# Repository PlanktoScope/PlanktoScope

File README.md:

# PlanktoScope: Open and Affordable Quantitative Imaging Platform

## What are Plankton?

_"Drifting endlessly, midway between the sea of air above and the depths of the abyss below, these strange creatures and the marine inflorescence that sustains them are called 'plankton' — the wanderers"_ - **[Rachel Carson](https://en.wikipedia.org/wiki/Rachel_Carson)**

Plankton are tiny organisms that drift in the oceans and play a crucial role in the global ecosystem. They are responsible for fixing 30-50% of the world's carbon dioxide and form the foundation of the global food chain. Despite their importance, studying plankton can be challenging due to the vast area of the oceans and the limited resources of research fleets and specialized equipment. The PlanktoScope is an open-source hardware and software platform that aims to make it easier to study plankton by providing high-throughput quantitative imaging capabilities at a low cost.

## What is a PlanktoScope?

The PlanktoScope is a modular, open-source platform for high-throughput quantitative imaging of plankton samples. Its small size, ease of use, and low cost make it suitable for a variety of applications, including the monitoring of laboratory cultures or natural micro-plankton communities. It can be controlled from any WiFi-enabled device and can be easily reconfigured to meet the changing needs of the user.

[Learn more about how it works](https://www.planktoscope.org/how-it-works)

## Read the Paper

The PlanktoScope has been described in the article ["PlanktoScope: Affordable Modular Quantitative Imaging Platform for Citizen Oceanography"](https://www.frontiersin.org/articles/10.3389/fmars.2022.949428/full), published in Frontiers in Marine Science in July 2022.

DOI: [https://doi.org/10.3389/fmars.2022.949428](https://doi.org/10.3389/fmars.2022.949428)

## Key Features

Here are some key features of the PlanktoScope:

1. **Low cost**: The PlanktoScope is designed to be affordable, with parts costing under $1000.
2. **Modular**: The PlanktoScope is modular, meaning it can be easily reconfigured to meet the changing needs of users.
3. **Open-source**: The PlanktoScope is based on open-source hardware and software, making it accessible to a wide community of engineers, researchers, and citizens.
4. **Versatility**: The PlanktoScope is versatile, and can be used to study a variety of plankton types, including laboratory cultures and natural micro-plankton communities.
5. **High-throughput**: The PlanktoScope is capable of high-throughput quantitative imaging, allowing users to analyze large numbers of samples quickly and efficiently.
6. **WiFi-enabled**: The PlanktoScope can be controlled from any WiFi-enabled device, making it easy to use and deploy in a variety of settings.
7. **Portable**: The PlanktoScope is small and portable, making it easy to transport and use in the field.
8. **Ease of use**: The PlanktoScope is designed to be easy to use, with instructions for assembly and use available on the PlanktoScope website.

## How do I get one?

You can access the complete documentation here: https://planktoscope.github.io/PlanktoScope/
|Get the kit|Assemble your kit|Start your machine|
|--|--|--|
||||

## Getting Involved

There are several ways you can join the development effort and contribute to this project.

### Communication Platform

We use Slack as a communication platform for interested parties. You can request to join by filling out [this form](https://docs.google.com/forms/d/e/1FAIpQLSfcod-avpzWVmWj42_hW1v2mMSHm0DAGXHxVECFig2dnKHxGQ/viewform).

### Reporting Issues

If you have identified a bug in the software or hardware, please open an issue in this repository to report it.

### Contributing to Development

You can also contribute to the development effort by working on open issues. Check out the [issues labeled as good first issues](https://github.com/PlanktoScope/PlanktoScope/labels/good%20first%20issue) and let us know in the comments if you are interested in working on one. We may be able to provide guidance as you get started with the code.

## License Information

This repository contains various types of materials that are covered by different licenses. Please read the following information carefully to determine which license applies to the materials you wish to use.

### Hardware Files

All hardware files and documentation located in the `hardware` directory are released under the [CERN-OHL-S-2.0](https://ohwr.org/cern_ohl_s_v2.txt) license.

### Software Source Code

The source code is released under the [GPL-3.0](https://www.gnu.org/licenses/gpl-3.0.en.html) license.

### Other Materials

All other materials, including documentation and pictures, are released under the [Creative Commons CC-BY-SA 4.0](https://creativecommons.org/licenses/by-sa/4.0/) license.

If you wish to use any of the materials in this repository for a project that cannot be open-sourced, please contact us using Slack so we can discuss potential solutions.

We encourage you to fork this repository and publish any improvements you make. Doing so helps others and allows us to potentially integrate your changes into this repository.

## Citing PlanktoScope

If you use PlanktoScope in your research, please use the following BibTeX entry.

```
@article{Pollina2022PlanktoScope,
  author={Pollina, Thibaut and Larson, Adam G. and Lombard, Fabien and Li, Hongquan and Le Guen, David and Colin, Sébastien and de Vargas, Colomban and Prakash, Manu},
  title={PlanktoScope: Affordable Modular Quantitative Imaging Platform for Citizen Oceanography},
  journal={Frontiers in Marine Science},
  year={2022},
  doi={10.3389/fmars.2022.949428}
}
```

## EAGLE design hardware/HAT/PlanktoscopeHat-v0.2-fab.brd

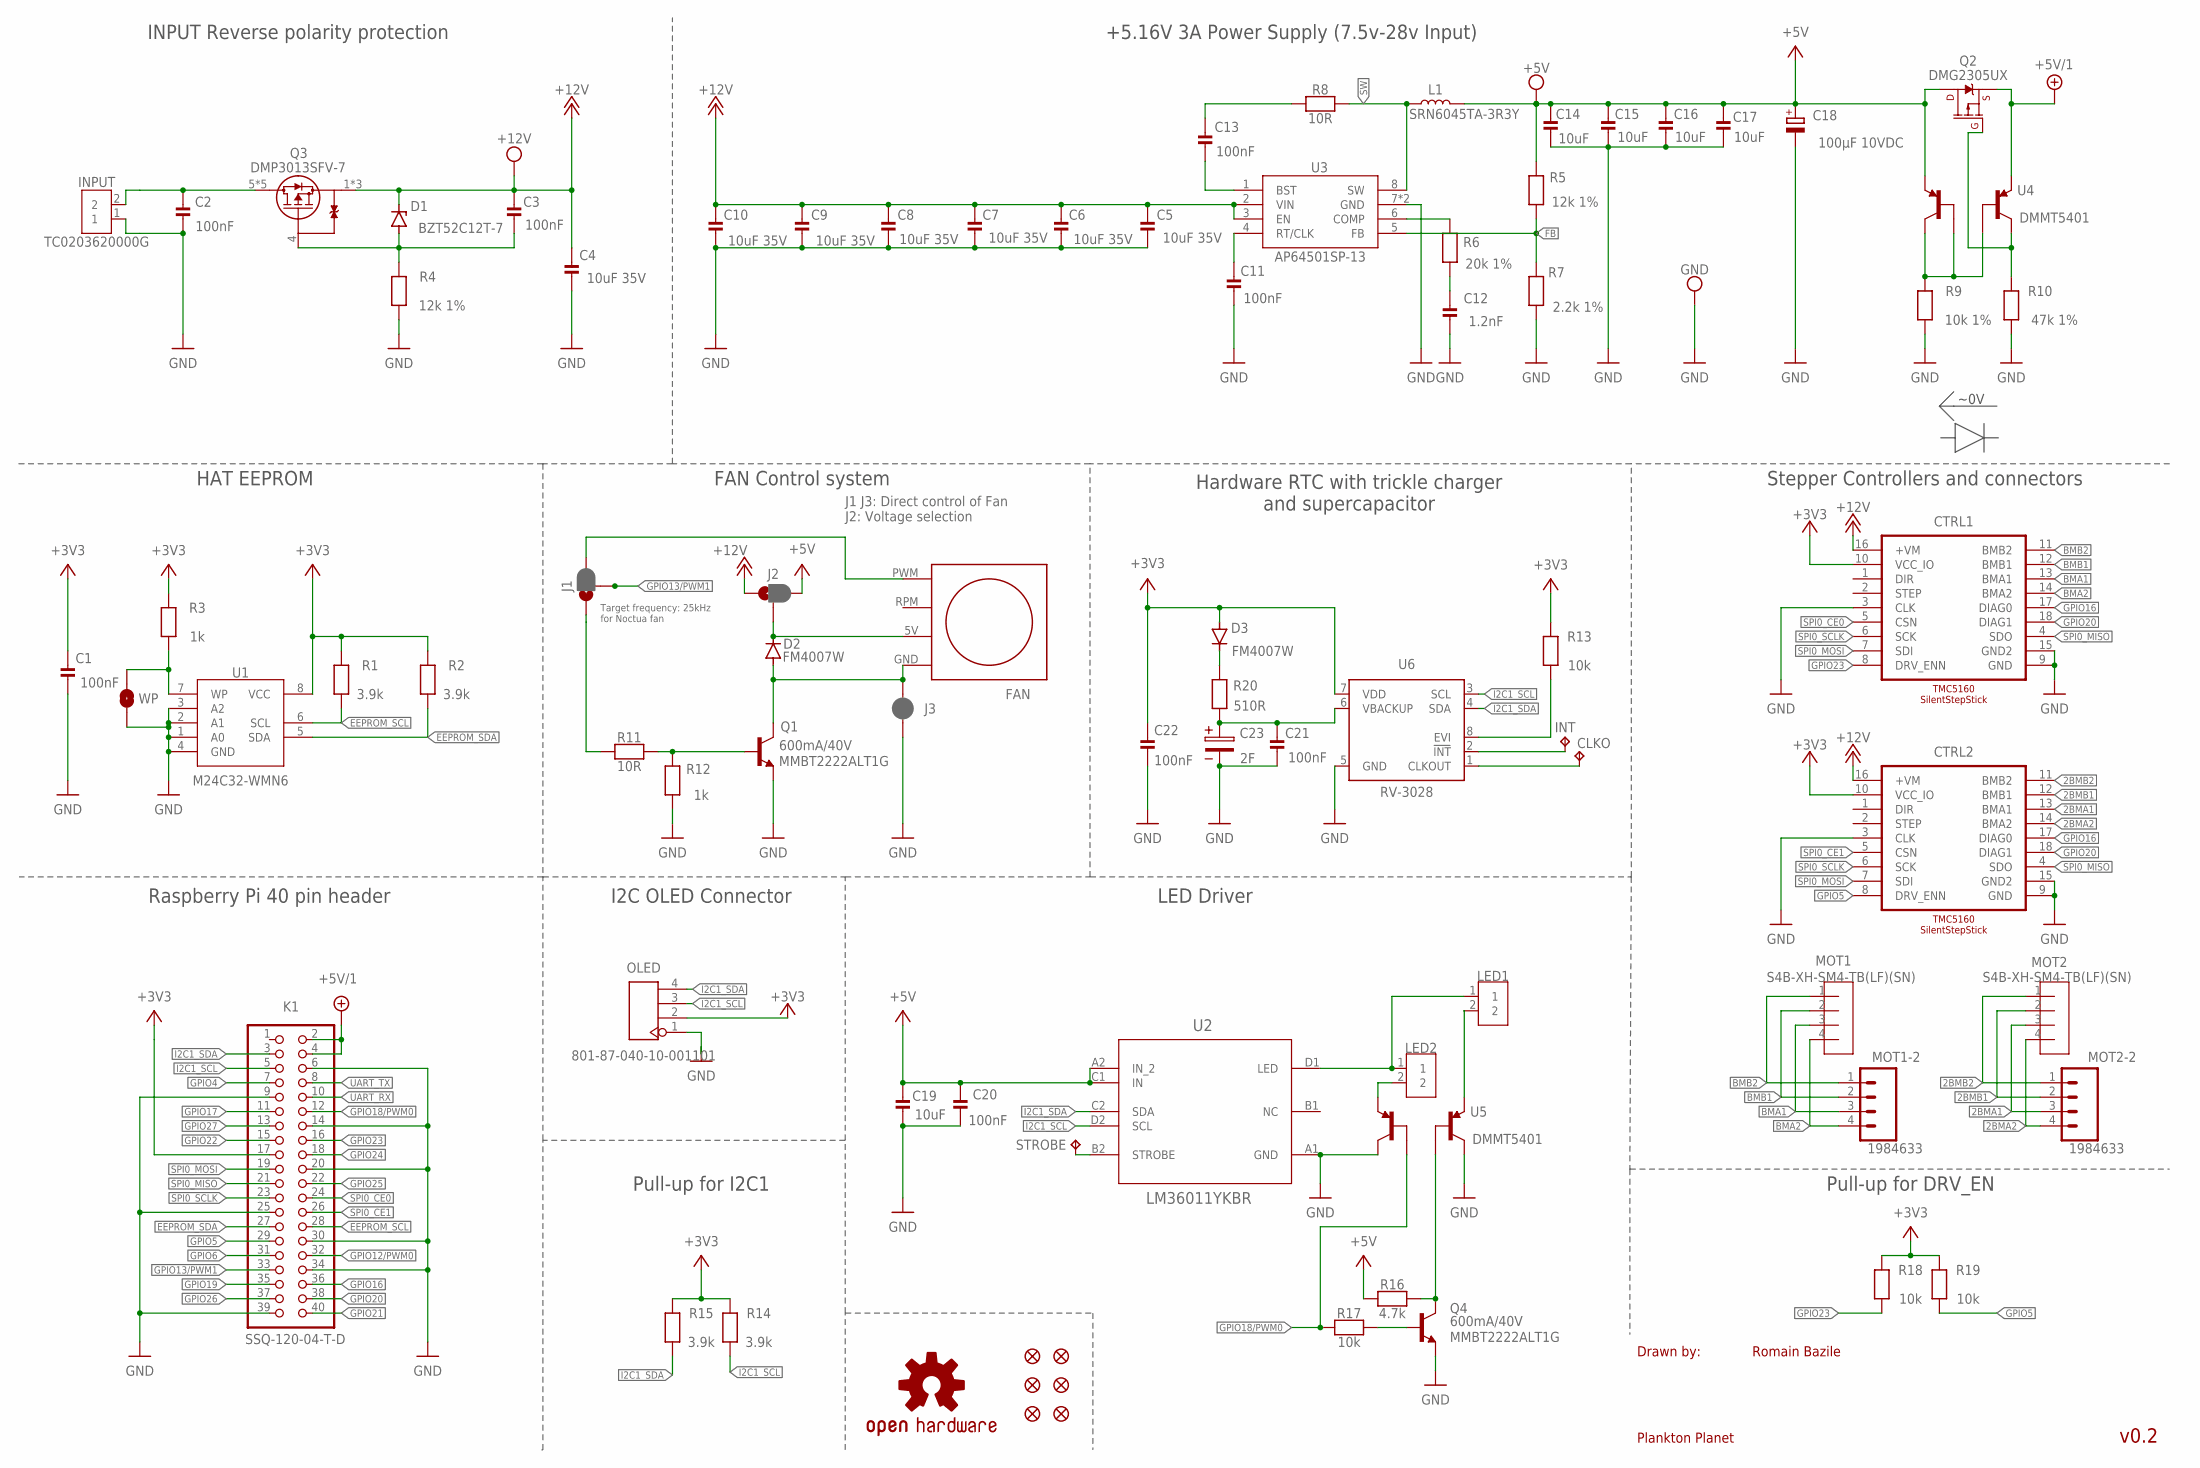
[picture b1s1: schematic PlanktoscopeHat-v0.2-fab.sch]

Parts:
+5V, +12V: TESTPOINTPAD2MM; TESTPOINT_PAD_2MM
C1, C2, C3, C11, C13, C20, C21, C22: 100nF; _0805MP
C4, C5, C6, C7, C8, C9, C10: 10uF 35V; _0805MP
C12: 1.2nF; _0805MP
C14, C15, C16, C17, C19: 10uF; _0805MP
C18: 100µF 10VDC; CAPMP6032X280N; MPN TPSC107K010T0200
C23: 2F; 8X3.5X0.9(DXAXB); MPN SCCR12E105SRB
CLKO: TPB1,27; B1,27
CTRL1, CTRL2: TMC5160_SILENTSTEPSTICK; TMC5160_STEPSTICK
D1: BZT52C12T-7; SODFL1608X70
D2, D3: FM4007W; DO-214AC
FAN: 40MM_FAN
FD1, FD2, FD3, FD4, FD5, FD6: FIDUCIAL1X2; FIDUCIAL-1X2
GND: TESTPOINTPAD2MM; TESTPOINT_PAD_2MM
INPUT: TC0203620000G; TERMBLK_508-2N; MPN TC0203620000G
INT: TPB1,27; B1,27
J1, J2: JUMPER-SMT_3_1-NC_PASTE_SILK; SMT-JUMPER_3_1-NC_PASTE_SILK
J3: JUMPER-SMT_2_NC_PASTE_SILK; SMT-JUMPER_2_NC_PASTE_SILK
K1: SSQ-120-04-T-D; 2X20
L1: SRN6045TA-3R3Y; SRN6045
LED1, LED2: 2828XX-2282834-2; TERMBLK_254-2N
LOGO1: OSHW-LOGOL; OSHW-LOGO-L
MOT1, MOT2: S4B-XH-SM4-TB(LF)(SN); CONN_S4B-XH-SM4-TB_JST; MPN S4B-XH-SM4-TB(LF)(SN)
MOT1-2, MOT2-2: 1984633; SCREWTERMINAL-3.5MM-4
OLED: 801-87-040-10-001101; H4-2.54
Q1, Q4: 600mA/40V; SOT23-3; MPN MMBT2222ALT1G
Q2: DMG2305UX; SOT23-3
Q3: DMP3013SFV-7; POWERDI3333-8_UX_DIO
R1, R2, R14, R15: 3.9k; _0805MP
R3, R12: 1k; _0805MP
R4, R5: 12k 1%; _0805MP
R6: 20k 1%; _0805MP
R7: 2.2k 1%; _0805MP
R8, R11: 10R; _0805MP
R9: 10k 1%; _0805MP
R10: 47k 1%; _0805MP
R13, R17, R18, R19: 10k; _0805MP
R16: 4.7k; _0805MP
R20: 510R; _0805MP
STROBE: TPTP15R; TP15R
U1: M24C32-WMN6; SO-8_STM
U2: LM36011YKBR; YKB0008AGAG
U3: AP64501SP-13; SO-8EP_DIO
U4, U5: DMMT5401; SOT26
U6: RV-3028
WP: JUMPER-SMT_2_NO_SILK; SMT-JUMPER_2_NO_SILK

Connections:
2BMA1: CTRL2.13 (BMA1), MOT2.3, MOT2-2.3
2BMA2: CTRL2.14 (BMA2), MOT2.4, MOT2-2.4
2BMB1: CTRL2.12 (BMB1), MOT2.2, MOT2-2.2
2BMB2: CTRL2.11 (BMB2), MOT2.1, MOT2-2.1
+3V3: C1.1, C22.1, CTRL1.10 (VCC_IO), CTRL2.10 (VCC_IO), D3.A, K1.17, OLED.2, R1.2, R2.2, R3.2, R13.2, R14.2, R15.2, R18.2, R19.2, U1.8 (VCC), U6.7 (VDD)
+5V: +5V.P$1, C14.1, C15.1, C16.1, C17.1, C18.1 (+), C19.1, C20.1, J2.3, L1.2, Q2.3 (D), R5.2, R16.2, U2.A2 (IN_2), U2.C1 (IN), U4.D1 (6)
+5V/1: K1.2, K1.4, Q2.2 (S), U4.S1 (5)
+12V: +12V.P$1, C3.1, C4.1, C5.1, C6.1, C7.1, C8.1, C9.1, C10.1, CTRL1.16 (+VM), CTRL2.16 (+VM), D1.1 (C), J2.1, Q3.1 (S), Q3.2 (S), Q3.3 (S), U3.2 (VIN), U3.3 (EN)
/GPIO18: Q4.3 (C), R16.1, U5.G2 (3)
/INT: INT.TP, U6.2 (!INT)
BMA1: CTRL1.13 (BMA1), MOT1.3, MOT1-2.3
BMA2: CTRL1.14 (BMA2), MOT1.4, MOT1-2.4
BMB1: CTRL1.12 (BMB1), MOT1.2, MOT1-2.2
BMB2: CTRL1.11 (BMB2), MOT1.1, MOT1-2.1
BST: C13.2, U3.1 (BST)
CLKOUT: CLKO.TP, U6.1 (CLKOUT)
COMP: R6.2, U3.6 (COMP)
EEPROM_SCL: K1.28, R1.1, U1.6 (SCL)
EEPROM_SDA: K1.27, R2.1, U1.5 (SDA)
FB: R5.1, R7.2, U3.5 (FB)
GND: C1.2, C2.2, C4.2, C5.2, C6.2, C7.2, C8.2, C9.2, C10.2, C11.2, C12.2, C14.2, C15.2, C16.2, C17.2, C18.2 (-), C19.2, C20.2, C21.2, C22.2, C23.2, CTRL1.3 (CLK), CTRL1.9 (GND), CTRL1.15 (GND2), CTRL2.3 (CLK), CTRL2.9 (GND), CTRL2.15 (GND2), GND.P$1, INPUT.1, J3.1, K1.6, K1.9, K1.14, K1.20, K1.25, K1.30, K1.34, K1.39, OLED.1, Q1.2 (E), Q4.2 (E), R4.1, R7.1, R9.1, R10.1, R12.1, U1.1 (A0), U1.2 (A1), U1.3 (A2), U1.4 (GND), U2.A1 (GND), U3.7 (GND), U3.EPAD (GND), U5.D2 (4), U5.G1 (1), U6.5 (GND), WP.1
GPIO4: K1.7
GPIO5: CTRL2.8 (DRV_ENN), K1.29, R19.1
GPIO6: K1.31
GPIO12/PWM0: K1.32
GPIO13/PWM1: J1.2, K1.33
GPIO16: CTRL1.17 (DIAG0), CTRL2.17 (DIAG0), K1.36
GPIO17: K1.11
GPIO18/PWM0: K1.12, R17.1, U5.S2 (2)
GPIO19: K1.35
GPIO20: CTRL1.18 (DIAG1), CTRL2.18 (DIAG1), K1.38
GPIO21: K1.40
GPIO22: K1.15
GPIO23: CTRL1.8 (DRV_ENN), K1.16, R18.1
GPIO24: K1.18
GPIO25: K1.22
GPIO26: K1.37
GPIO27: K1.13
I2C1_SCL: K1.5, OLED.3, R14.1, U2.D2 (SCL), U6.3 (SCL)
I2C1_SDA: K1.3, OLED.4, R15.1, U2.C2 (SDA), U6.4 (SDA)
LED: LED1.1, LED2.1, U2.D1 (LED)
LED1OUT: LED1.2, U5.S1 (5)
LED2OUT: LED2.2, U5.D1 (6)
unnamed: R3.1, U1.7 (WP), WP.2
unnamed: STROBE.TP, U2.B2 (STROBE)
unnamed: C3.2, D1.2 (A), Q3.4 (G), R4.2
unnamed: D2.A, FAN.GND, J3.2, Q1.3 (C)
unnamed: C13.1, R8.2
unnamed: Q2.1 (G), R10.2, U4.D2 (4)
unnamed: C12.1, R6.1
unnamed: R9.2, U4.G1 (1), U4.G2 (3), U4.S2 (2)
unnamed: D2.C, FAN.5V (+5V), J2.2
unnamed: Q1.1 (B), R11.2, R12.2
unnamed: J1.1, R11.1
unnamed: FAN.PWM, J1.3
unnamed: D3.C, R20.2
unnamed: R13.1, U6.8 (EVI)
unnamed: Q4.1 (B), R17.2
RT: C11.1, U3.4 (RT/CLK)
SPI0_CE0: CTRL1.5 (CSN), K1.24
SPI0_CE1: CTRL2.5 (CSN), K1.26
SPI0_MISO: CTRL1.4 (SDO), CTRL2.4 (SDO), K1.21
SPI0_MOSI: CTRL1.7 (SDI), CTRL2.7 (SDI), K1.19
SPI0_SCLK: CTRL1.6 (SCK), CTRL2.6 (SCK), K1.23
SW: L1.1, R8.1, U3.8 (SW)
UART_RX: K1.10
UART_TX: K1.8
VBACKUP: C21.1, C23.1, R20.1, U6.6 (VBACKUP)
VIN: C2.1, INPUT.2, Q3.5 (D), Q3.6 (D), Q3.7 (D), Q3.8 (D), Q3.9 (D)

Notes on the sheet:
Drawn by:
Plankton Planet
Romain Bazile
v0.2
~0V
+5.16V 3A Power Supply (7.5v-28v Input)
Pull-up for DRV_EN
Pull-up for I2C1
HAT EEPROM
LED Driver
INPUT Reverse polarity protection
FAN Control system
Hardware RTC with trickle charger and supercapacitor
Stepper Controllers and connectors
I2C OLED Connector
Raspberry Pi 40 pin header
J1 J3: Direct control of Fan J2: Voltage selection
Target frequency: 25kHz for Noctua fan

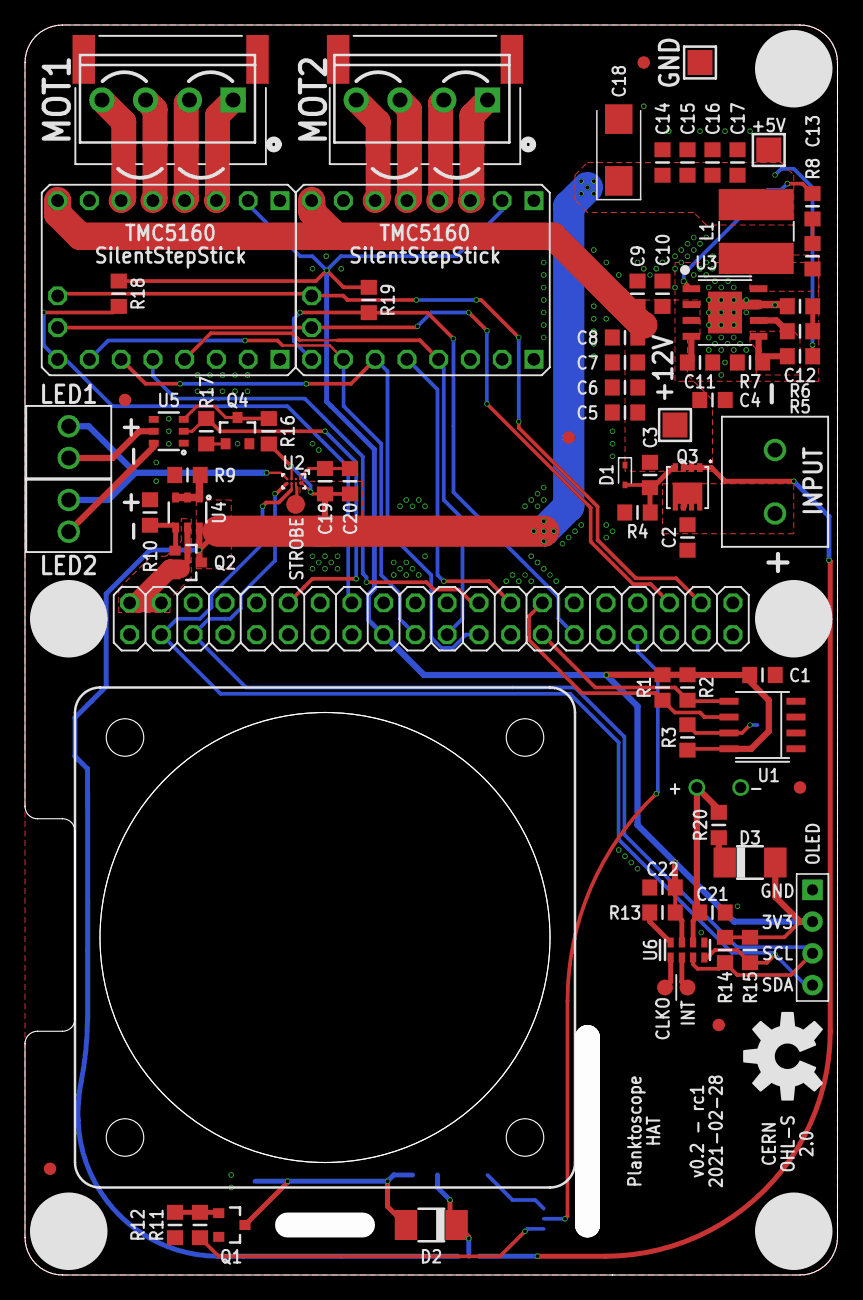
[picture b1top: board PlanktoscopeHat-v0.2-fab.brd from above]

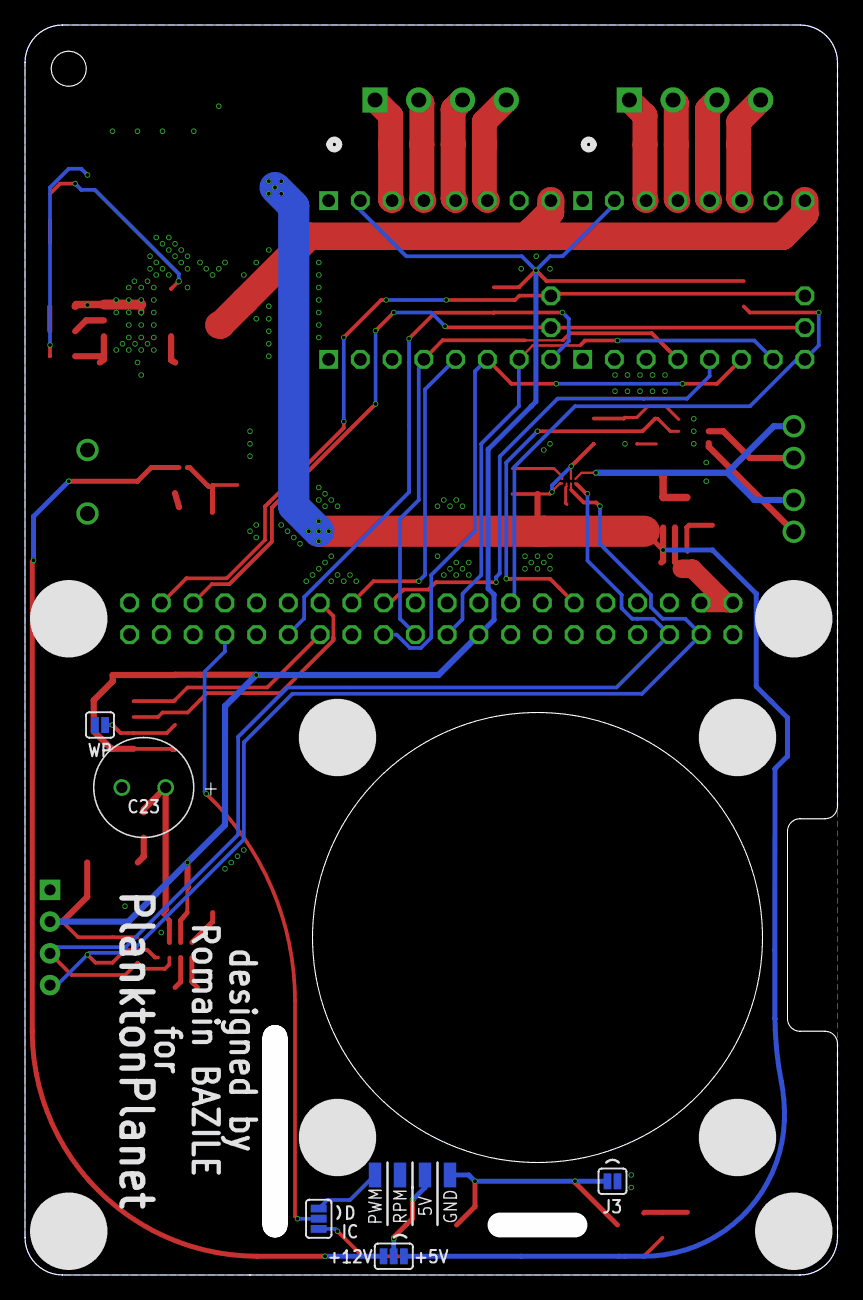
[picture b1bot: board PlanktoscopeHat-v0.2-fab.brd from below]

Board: 2 copper layers, 65.0 x 100.0 mm, 86 parts (5 on the bottom side), 56 nets.

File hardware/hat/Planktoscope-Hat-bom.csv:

Qty,Value,Device,Parts,MANUFACTURER,MANUFACTURER_PART_NUMBER
1,1.2nF,CAP_CERAMIC_0805MP,C12,,C0805C122K5RACTU
8,100nF,CAP_CERAMIC_0805MP,"C1, C2, C3, C11, C13, C19, C21, C22",,CL21B104KCFNNNE
1,100µF 10VDC,C-POL_TANTALUM-2412(6032-METRIC),C18,,TPSC107K010R0075
1,10R,RESISTOR_0805MP,R8,,CRCW080510R0FKEAC 
4,10k 1%,RESISTOR_0805MP,"R9, R17, R18, R19",,CRCW080510K0FKEAC
5,10uF,CAP_CERAMIC_0805MP,"C14, C15, C16, C17, C20",,CL21A106KOQNNWE
7,10uF 35V,CAP_CERAMIC_0805MP,"C4, C5, C6, C7, C8, C9, C10",,C2012X5R1V106M085AC
2,12k 1%,RESISTOR_0805MP,"R4, R5",,CRCW080512K0FKEA
1,1k,RESISTOR_0805MP,R3,,CRCW08051K00FKEAC 
1,2.2k 1%,RESISTOR_0805MP,R7,,CRGCQ0805F2K2
1,20k 1%,RESISTOR_0805MP,R6,,CRCW080520K0FKEAC 
4,3.9k,RESISTOR_0805MP,"R1, R2, R14, R15",,CRCW08053K90FKEA
1,4.7k,RESISTOR_0805MP,R16,,CR0805-FX-4701ELF 
1,47k 1%,RESISTOR_0805MP,R10,,CRGCQ0805F47K
1,5.1k,RESISTOR_0805MP,R12,,RC0805FR-075K1L 
2,510R,RESISTOR_0805MP,"R11, R20",,AC0805FR-07511RL 
2,MMBT2222ALT1G,MMBT2222ALT1G,"Q1, Q4",,MMBT2222ALT1G
1,9HT12-32.768KDZY-T,9HT12,Q5,,9HT12-32.768KDZY-T
1,AP64501SP-13,AP64500SP-13,U3,,AP64500SP-13
1,BZT52C12TQ-7-F,BZT52C12TQ-7-F,D1,,BZT52C12TQ-7-F
1,"PMV33UPE,215","PMV33UPE,215",Q2,,"PMV33UPE,215"
2,BC857S-TP,BC857S-TP,"U4, U5",,BC857S-TP
1,SI7101DN,SI7101DN,Q3,Vishay,SI7101DN-T1-GE3
2,FM4007W,DIODE-DO-214AC,"D2, D3",,
1,LM36011YKBR,LM36011YKBR,U2,Texas Instruments,LM36011YKBR
1,M24C32-WMN6,M24C32-WMN6,U1,,M24C32-WMN6
1,PCF85363ATL,PCF85363ATL,U6,NXP,PCF85363ATL/A
1,SRN6045TA-3R3Y,INDUCTOR-SRN6045-33UH,L1,,SRN6045TA-3R3Y

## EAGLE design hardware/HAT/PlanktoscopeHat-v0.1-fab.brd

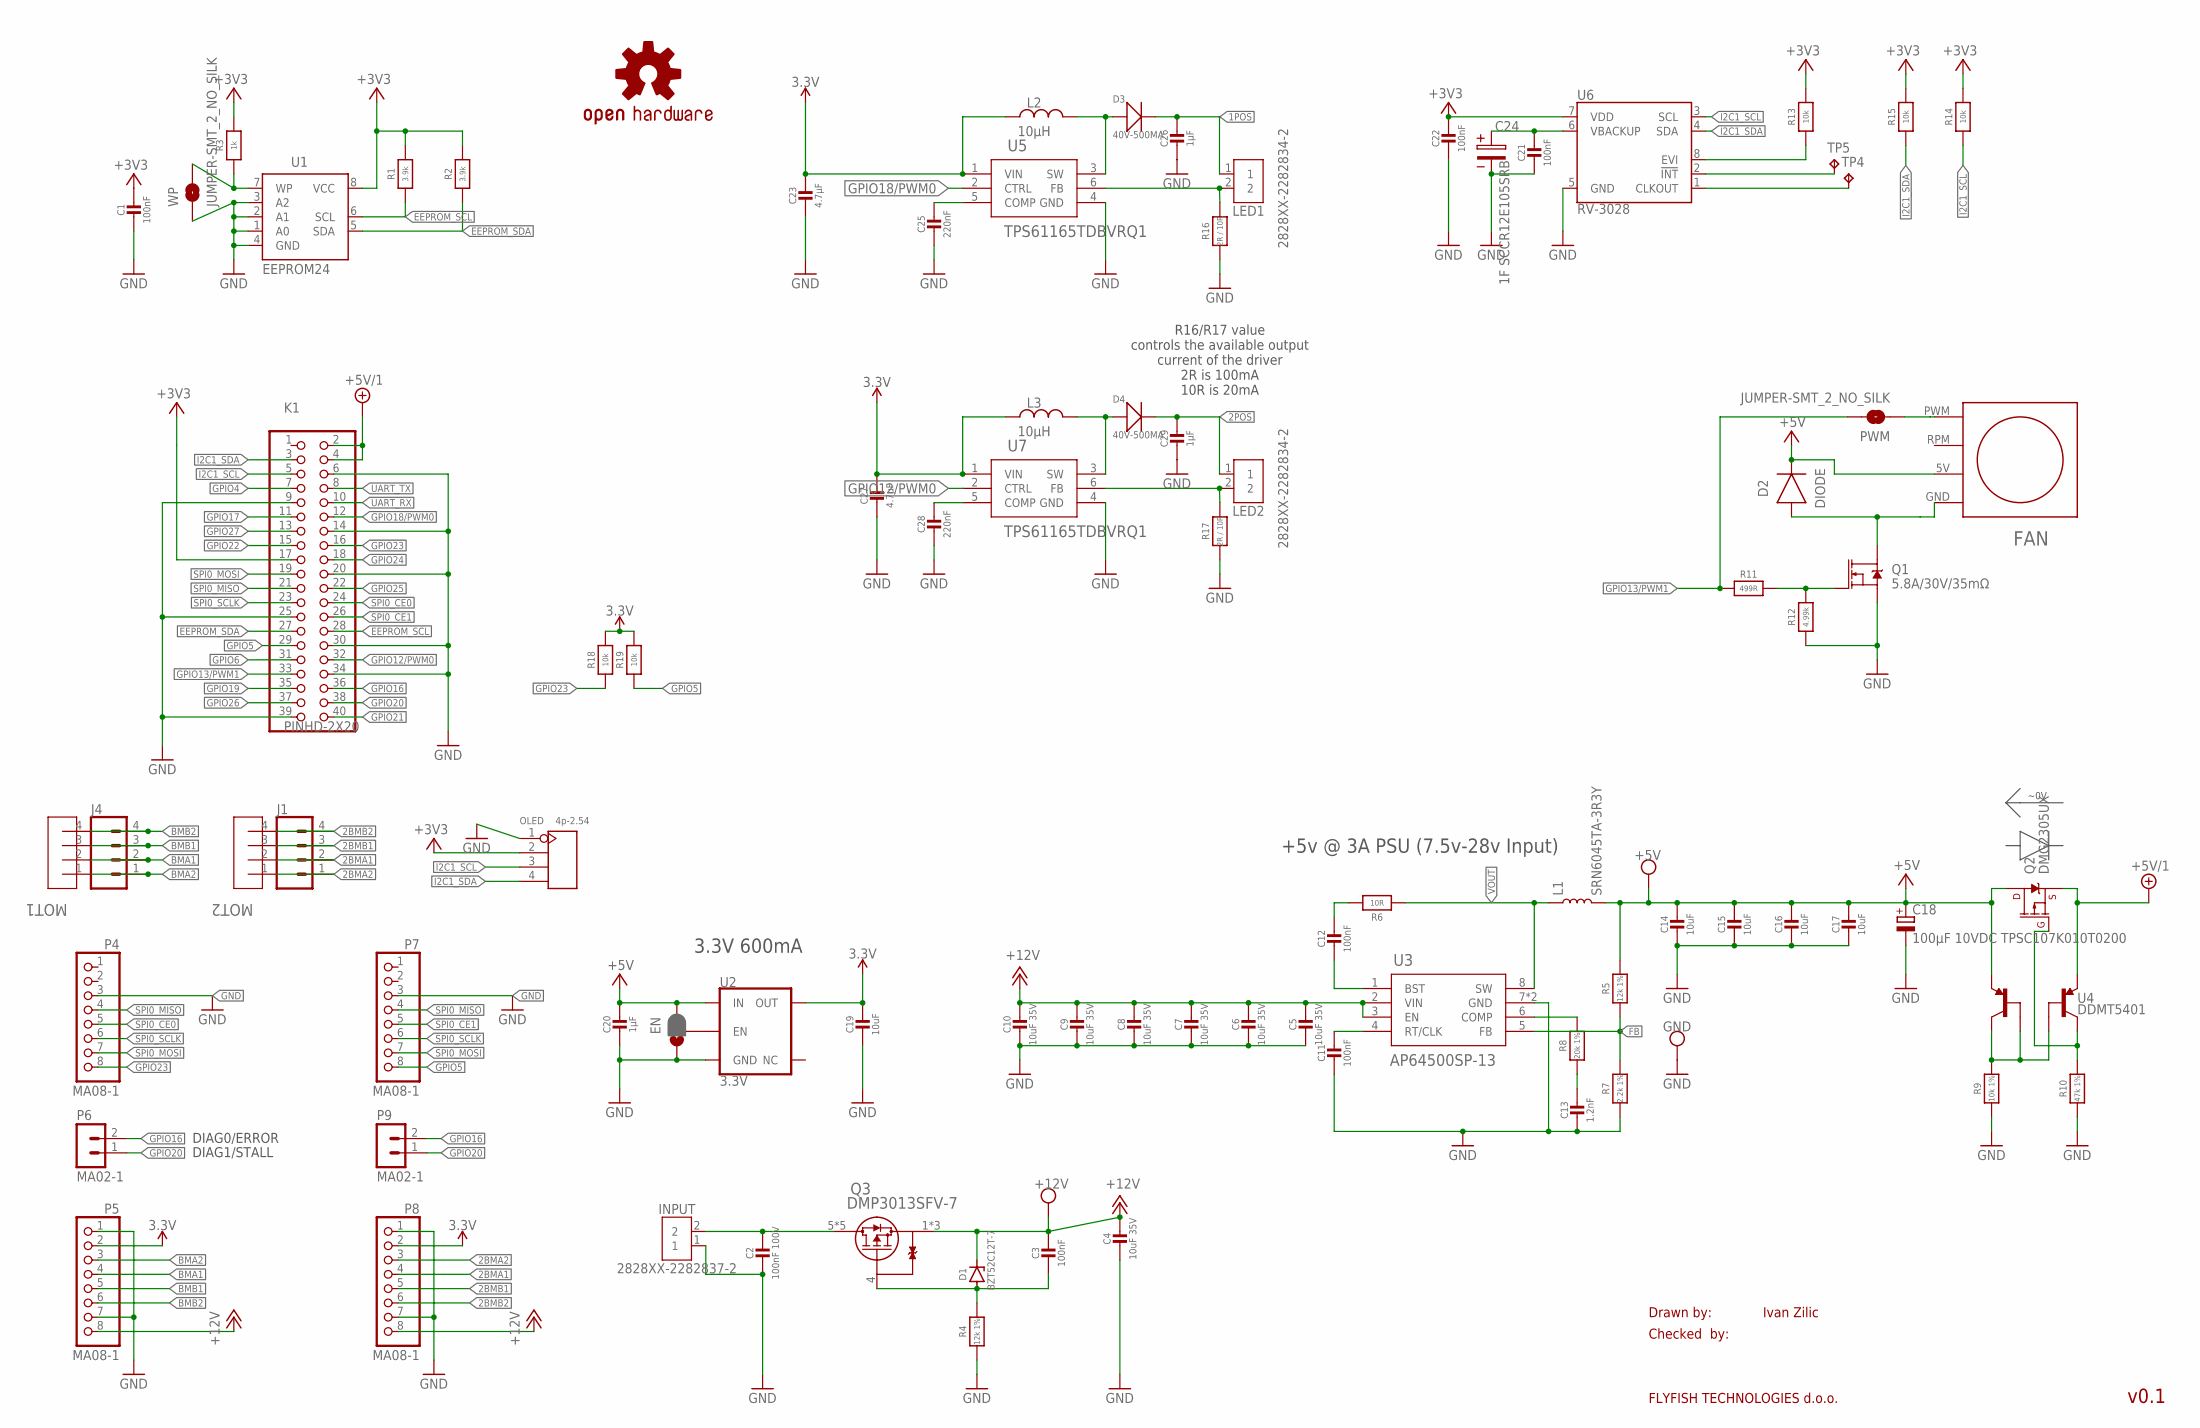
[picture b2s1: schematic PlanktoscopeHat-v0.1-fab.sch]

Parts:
+5V, +12V: TESTPOINTPAD2MM; TESTPOINT_PAD_2MM
C1, C3, C11, C12, C21, C22: 100nF; _0805MP
C2: 100nF 100V; _0805MP
C4, C5, C6, C7, C8, C9, C10: 10uF 35V; _0805MP
C13: 1.2nF; _0805MP
C14, C15, C16, C17, C19: 10uF; _0805MP
C18: 100µF 10VDC TPSC107K010T0200; CAPMP6032X280N
C20, C26, C29: 1µF; _0805MP
C23, C27: 4.7µF; _0805MP
C24: 1F SCCR12E105SRB; 8X3.5X0.9(DXAXB)
C25, C28: 220nF; _0805MP
D1: BZT52C12T-7; SODFL1608X70
D2: DIODE; DIOM5226X290N
D3, D4: 40V-500MA; SOD-123
EN: JUMPER-SMT_3_1-NC_PASTE_SILK; SMT-JUMPER_3_1-NC_PASTE_SILK
FAN: 40MM_FAN
GND: TESTPOINTPAD2MM; TESTPOINT_PAD_2MM
INPUT: 2828XX-2282837-2; TERMBLK_508-2N; MPN TC0203620000G
J1, J4: CONN_04SCREW; SCREWTERMINAL-3.5MM-4
K1: PINHD-2X20; 2X20
L1: SRN6045TA-3R3Y; SRN6045
L2, L3: 10µH; INDM3225X240; MPN CBC3225T100KR
LED1, LED2: 2828XX-2282834-2; TERMBLK_254-2N
LOGO1: OSHW-LOGOL-COPPER; OSHW-LOGO-L_COPPER
MOT1, MOT2: S4B-XH-SM4-TB(LF)(SN); CONN_S4B-XH-SM4-TB_JST
OLED: 4p-2.54; H4-2.54
P4, P5, P7, P8: MA08-1; 1X08-S
P6, P9: MA02-1
PWM: JUMPER-SMT_2_NO_SILK; SMT-JUMPER_2_NO_SILK
Q1: 5.8A/30V/35mΩ; SOT23-3
Q2: DMG2305UX; SOT23-3
Q3: DMP3013SFV-7; POWERDI3333-8_UX_DIO
R1, R2: 3.9k; _0805MP
R3: 1k; _0805MP
R4, R5: 12k 1%; _0805MP
R6: 10R; _0805MP
R7: 2.2k 1%; _0805MP
R8: 20k 1%; _0805MP
R9: 10k 1%; _0805MP
R10: 47k 1%; _0805MP
R11: 499R; _0805MP
R12: 4.99k; _0805MP
R13, R14, R15, R18, R19: 10k; _0805MP
R16, R17: 2R / 10R; _0805MP
TP4, TP5: TPB1,27; B1,27
U1: EEPROM24; SOIC8
U2: 3.3V; SOT23-5
U3: AP64500SP-13; SO-8EP_DIO
U4: DDMT5401; SOT26
U5, U7: TPS61165TDBVRQ1; DBV6
U6: RV-3028
WP: JUMPER-SMT_2_NO_SILK; SMT-JUMPER_2_NO_SILK

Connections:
1POS: C26.1, D3.-, LED1.1
2BMA1: J1.2, MOT2.2, P8.4
2BMA2: J1.1, MOT2.1, P8.3
2BMB1: J1.3, MOT2.3, P8.5
2BMB2: J1.4, MOT2.4, P8.6
2POS: C29.1, D4.-, LED2.1
3.3V: C19.1, C23.1, C27.1, L2.1, L3.1, P5.2, P8.2, R18.2, R19.2, U2.5 (OUT), U5.1 (VIN), U7.1 (VIN)
+3V3: C1.1, C22.1, K1.17, OLED.2, R1.2, R2.2, R3.2, R13.2, R14.2, R15.2, U1.8 (VCC), U6.7 (VDD)
+5V: +5V.P$1, C14.1, C15.1, C16.1, C17.1, C18.1 (+), C20.1, D2.1 (C), EN.3, FAN.5V (+5V), L1.2, Q2.3 (D), R5.2, U2.1 (IN), U4.D1 (6)
+5V/1: K1.2, K1.4, Q2.2 (S), U4.S1 (5)
+12V: +12V.P$1, C3.1, C4.1, C5.1, C6.1, C7.1, C8.1, C9.1, C10.1, D1.1 (C), P5.8, P8.8, Q3.1 (S), Q3.2 (S), Q3.3 (S), U3.2 (VIN), U3.3 (EN)
/INT: TP5.TP, U6.2 (!INT)
BMA1: J4.2, MOT1.2, P5.4
BMA2: J4.1, MOT1.1, P5.3
BMB1: J4.3, MOT1.3, P5.5
BMB2: J4.4, MOT1.4, P5.6
CLKOUT: TP4.TP, U6.1 (CLKOUT)
COMP: R8.2, U3.6 (COMP)
EEPROM_SCL: K1.28, R1.1, U1.6 (SCL)
EEPROM_SDA: K1.27, R2.1, U1.5 (SDA)
FB: R5.1, R7.2, U3.5 (FB)
GND: C1.2, C2.2, C4.2, C5.2, C6.2, C7.2, C8.2, C9.2, C10.2, C11.2, C13.2, C14.2, C15.2, C16.2, C17.2, C18.2 (-), C19.2, C20.2, C21.2, C22.2, C23.2, C24.2, C25.2, C26.2, C27.2, C28.2, C29.2, EN.1, GND.P$1, INPUT.1, K1.6, K1.9, K1.14, K1.20, K1.25, K1.30, K1.34, K1.39, OLED.1, P4.3, P5.1, P5.7, P7.3, P8.1, P8.7, Q1.2 (S), R4.1, R7.1, R9.1, R10.1, R12.1, R16.1, R17.1, U1.1 (A0), U1.2 (A1), U1.3 (A2), U1.4 (GND), U2.2 (GND), U3.7 (GND), U3.EPAD (GND), U5.4 (GND), U6.5 (GND), U7.4 (GND), WP.1
GPIO4: K1.7
GPIO5: K1.29, P7.8, R19.1
GPIO6: K1.31
GPIO12/PWM0: K1.32, U7.2 (CTRL)
GPIO13/PWM1: K1.33, PWM.2, R11.1
GPIO16: K1.36, P6.2, P9.2
GPIO17: K1.11
GPIO18/PWM0: K1.12, U5.2 (CTRL)
GPIO19: K1.35
GPIO20: K1.38, P6.1, P9.1
GPIO21: K1.40
GPIO22: K1.15
GPIO23: K1.16, P4.8, R18.1
GPIO24: K1.18
GPIO25: K1.22
GPIO26: K1.37
GPIO27: K1.13
I2C1_SCL: K1.5, OLED.3, R14.1, U6.3 (SCL)
I2C1_SDA: K1.3, OLED.4, R15.1, U6.4 (SDA)
unnamed: R3.1, U1.7 (WP), WP.2
unnamed: C21.1, C24.1, U6.6 (VBACKUP)
unnamed: C3.2, D1.2 (A), Q3.4 (G), R4.2
unnamed: EN.2, U2.3 (EN)
unnamed: D2.2 (A), FAN.GND, Q1.3 (D)
unnamed: C12.2, U3.1 (BST)
unnamed: C12.1, R6.2
unnamed: Q2.1 (G), R10.2, U4.D2 (4)
unnamed: C11.1, U3.4 (RT/CLK)
unnamed: C13.1, R8.1
unnamed: R9.2, U4.G1 (1), U4.G2 (3), U4.S2 (2)
unnamed: Q1.1 (G), R11.2, R12.2
unnamed: FAN.PWM, PWM.1
unnamed: R13.1, U6.8 (EVI)
unnamed: C25.1, U5.5 (COMP)
unnamed: LED1.2, R16.2, U5.6 (FB)
unnamed: C28.1, U7.5 (COMP)
unnamed: D3.+, L2.2, U5.3 (SW)
unnamed: LED2.2, R17.2, U7.6 (FB)
unnamed: D4.+, L3.2, U7.3 (SW)
SPI0_CE0: K1.24, P4.5
SPI0_CE1: K1.26, P7.5
SPI0_MISO: K1.21, P4.4, P7.4
SPI0_MOSI: K1.19, P4.7, P7.7
SPI0_SCLK: K1.23, P4.6, P7.6
UART_RX: K1.10
UART_TX: K1.8
VIN: C2.1, INPUT.2, Q3.5 (D), Q3.6 (D), Q3.7 (D), Q3.8 (D), Q3.9 (D)
VOUT: L1.1, R6.1, U3.8 (SW)

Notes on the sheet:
Drawn by:
Checked by:
FLYFISH TECHNOLOGIES d.o.o.
Ivan Zilic
v0.1
~0V
3.3V 600mA
+5v @ 3A PSU (7.5v-28v Input)
DIAG0/ERROR
DIAG1/STALL
R16/R17 value controls the available output current of the driver 2R is 100mA 10R is 20mA

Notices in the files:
parts and their libraries:
SparkFun-IC-Power: Licensing: Creative Commons ShareAlike 4.0 International - https://creativecommons.org/licenses/by-sa/4.0
Wurth_Elektronik_Passive_Capacitors_rev1: Copyright: Würth Elektronik
COPYRIGHT: Copyright (C) 2018 Accelerated Designs. All rights reserved
